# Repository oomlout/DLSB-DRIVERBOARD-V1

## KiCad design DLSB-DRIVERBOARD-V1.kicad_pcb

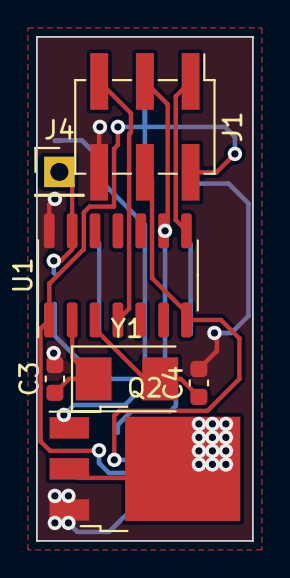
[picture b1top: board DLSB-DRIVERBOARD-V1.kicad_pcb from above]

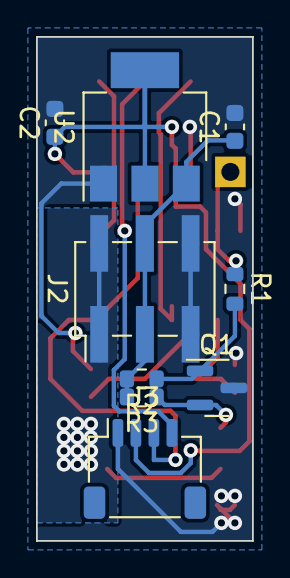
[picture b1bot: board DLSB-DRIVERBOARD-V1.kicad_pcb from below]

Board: 2 copper layers, 12.0 x 28.0 mm, 16 parts (9 on the bottom side), 13 nets.

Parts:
C1, C2: CAPC-0603-X-NF100-V50-C6N100
C3, C4: CAPC-0603-X-PF20-V50-C6P20
J1, J2: HEAD-I01-X-PI2X03-SM-H2X3SM
J3: HEAD-JSTSH-X-PI04-RS-HSH04RS
J4: HEAD-I01-X-PI01-01-HP01
Q1: TRNN-SO23-X-KS8050-01-TRNN-SO23-KS8050
Q2: MOSN-T252-X-K4184-01-MN2524184A
R1: RESE-0603-X-O271-01-R6O271
R2, R3: RESE-0603-X-O103-01-R6O1301
U1: MCUU-SC14-84-ATTINY-01-MCAT84SC14
U2: VREG-SO223-X-KLD1117-V33D-VR111722333
Y1: XTAL-5032-X-MZ16-01-XTAL5032-MZ16

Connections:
ADC0: J4.1, R1.1, U1.13 (PA0)
ADC4: J1.3, J3.4, U1.9 (PA4)
ADC5: J1.1, U1.8 (PA5)
ADC6: J1.4, J3.3, U1.7 (PA6)
CLKI: C3.1, U1.2 (PB0), Y1.1
GND: C1.2, C2.2, C3.2, C4.2, J1.6, J2.5, J2.6, J3.1, Q1.3 (C), Q2.3 (S), U1.14 (GND), U2.1 (GND)
unnamed: Q1.1 (B), R1.2, R2.1
unnamed: Q1.2 (E), Q2.1 (G), R3.1
OUTPUT01: J2.1, J2.2, Q2.2 (D)
PB1: C4.1, U1.3 (PB1), Y1.2
PB3: J1.5, U1.4 (~RESET/PB3)
VIN: C1.1, J2.3, J2.4, R2.2, R3.2, U2.3 (VI)
VOUT: C2.1, J1.2, J3.2, U1.1 (VCC), U2.2 (VO)

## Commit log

2022-11-18 Initial push.
2022-11-21 First PCB order.
2022-11-21 moved board to center of page.
